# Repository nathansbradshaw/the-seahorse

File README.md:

# The Seahorse v2 

34 key keyboard with TP

Link to ZMK code https://github.com/nathansbradshaw/zmk-the-seahorse

# BOM
These are links to what I bought, not necessary to get exactly the same

## items
- 4x (12 socket) [2.54mm Sockets (Cheap) - Recommended](https://www.amazon.com/gp/product/B0778TFL39/ref=ppx_yo_dt_b_search_asin_image?ie=UTF8&psc=1) or  [2.54mm Sockets (Quality)](https://www.mouser.com/ProductDetail/Mill-Max/315-43-112-41-003000?qs=s8Nb1z4Wn%2FRfWrVqQ0TOuQ%3D%3D)

- 48x [Mill Max Pins - Recommend (Digikey)](https://www.digikey.com/en/products/detail/3320-0-00-15-00-00-03-0/4147392)

- 34x [Choc Hot Swap Sockets](https://www.boardsource.xyz/products/Choc_Hot_Swap_Sockets)

- 34x Choc Switches

- 34x Choc Key caps

- 2x Nice!Nano or equivalent

- 34x [1N4148W-7-F - Diodes](https://www.digikey.com/en/products/detail/diodes-incorporated/1N4148W-7-F/814371)

- 2x [SSSS811101 - Battery Switch](https://www.digikey.com/en/products/detail/alps-alpine/SSSS811101/19529062?s=N4IgTCBcDaIMoLgDgIxoAwpAXQL5A)

- 2x [PTS636 SL43 LFS - Reset Switch](https://www.digikey.com/en/products/detail/c-k/PTS636-SL43-LFS/10071714)

- 2x [Lithium Battery 110mAh](https://typeractive.xyz/products/lithium-battery-110mah)

- 2x [JST Battery Jack](https://typeractive.xyz/products/battery-jack)

- 1x [T460s - Track Point (12 pin RED version)]()

- 1x [2005280120 - 12 pin 1.0mm Pitch (Note: Link might be wrong)](https://www.digikey.com/en/products/detail/molex/2005280120/12142065?s=N4IgTCBcDa4AxwKxgBwFo4EYxwAQgF0BfIA)

- 2x 1.8m screw and nut

# Estimated Cost to build (Updated July 3, 2024)

|Amount| | Item                    | Cost        |Salvageable|
|----|---|-------------------------|-------------|-----------|
| 2  |   | Reset Switch            | $0.20 USD   | No  |
| 2  |   | Nice!Nano               | $50.00 USD  | Yes |
| 2  |   | Lithium Battery 110mAh  | $6.00 USD   | Yes |
| 2  |   | JST Battery Jack        | $2.00 USD   | No  |
| 2  |   | Battery Switch          | $2.50       | No  |
| 34 |   | Choc Switches           | $27.00 USD  | Yes |
| 34 |   | Hot Swap Choc Sockets   | $5.10 USD   | No  |
| 34 |   | Choc Key cap            | $11.90 USD  | Yes |
| 34 |   | Diodes                  | $5.44 USD   | No  |
| 48 |   | Mill Max Pins           | $4.76 USD   | yes-ish|
| 4  |   | 2.54mm Sockets          | $1.60 USD   | No  |
| 1  |   | PCB                     | $10.00 USD  | No  |
| 1  |   | Track Point             | $10.00 USD  | Yes |
| 1  |   | FPC Cable               | Free w/ TP  | Yes |
| 1  |   | FPC connector           | $2.00 USD   | Yes |
 
-----

 Total Cost Without TP: **$121.74 USD**

 Total Cost With TP: **$133.77 USD**

---------

 Total Cost to upgrade: **$22.10 USD**

 Total Cost to upgrade with TP: **$24.10 USD**

# Loce Alda

## BOM
- 4x [Keystone 82 battery clip](https://www.digikey.com/en/products/detail/keystone-electronics/82/227467)
- 2x [XIAO nRF52840](https://www.seeedstudio.com/Seeed-XIAO-BLE-nRF52840-p-5201.html)
- 2x [74HC595 shift register](https://www.digikey.com/en/products/detail/texas-instruments/SN74HC595N/277246)?
- 34x Choc Switches
- 34x Choc Key caps
- 34x [1N4148W-7-F - Diodes](https://www.digikey.com/en/products/detail/diodes-incorporated/1N4148W-7-F/814371)
- 2x [SSSS811101 - Battery Switch](https://www.digikey.com/en/products/detail/alps-alpine/SSSS811101/19529062?s=N4IgTCBcDaIMoLgDgIxoAwpAXQL5A)
- 2x [PTS636 SL43 LFS - Reset Switch](https://www.digikey.com/en/products/detail/c-k/PTS636-SL43-LFS/10071714)
- 1x [T460s - Track Point (12 pin RED version)]()
- 1x [2005280120 - 12 pin 1.0mm Pitch (Note: Link might be wrong)](https://www.digikey.com/en/products/detail/molex/2005280120/12142065?s=N4IgTCBcDa4AxwKxgBwFo4EYxwAQgF0BfIA)
- 2x 1.8m screw and nut

|Amount| | Item                    | Cost        |Salvageable|
|----|---|-------------------------|-------------|-----------|
| 2  |   | Reset Switch            | $0.20 USD   | No  |
| 2  |   | XIAO nRF5284            | $20.00 USD  | NO  |
| 2  |   | Battery Switch          | $2.50       | No  |
| 34 |   | Choc 
| 34 |   | Hot Swap Choc Sockets   | $5.10 USD   | No  |
| 34 |   | Choc Key cap            | $11.90 USD  | Yes |
| 34 |   | Diodes                  | $5.44 USD   | No  |
| 1  |   | PCB                     | $10.00 USD  | No  |
| 1  |   | Track Point             | $10.00 USD  | Yes |
| 1  |   | FPC Cable               | Free w/ TP  | Yes |
| 1  |   | FPC connector           | $2.00 USD   | Yes |
| 2  |   | 74HC595 Shift Register  | $3.00 USD   | No  |
| 4  |   | Keystone 82 battery clip| $1.50 USD   | NO  |
| 2  |   | 10440 Lithium battery   | $5          | Yes |

-----

 Total Cost Without TP: **$64.91 USD**

 Total Cost With TP: **$76.91 USD**

---------

 Total Cost to upgrade: **$45.24 USD**

 Total Cost to upgrade with TP: **$47.24 USD**

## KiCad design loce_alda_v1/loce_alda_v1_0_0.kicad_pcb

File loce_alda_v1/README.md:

# The Seahorse v2 

34 key keyboard with TP

Link to ZMK code https://github.com/nathansbradshaw/zmk-the-seahorse

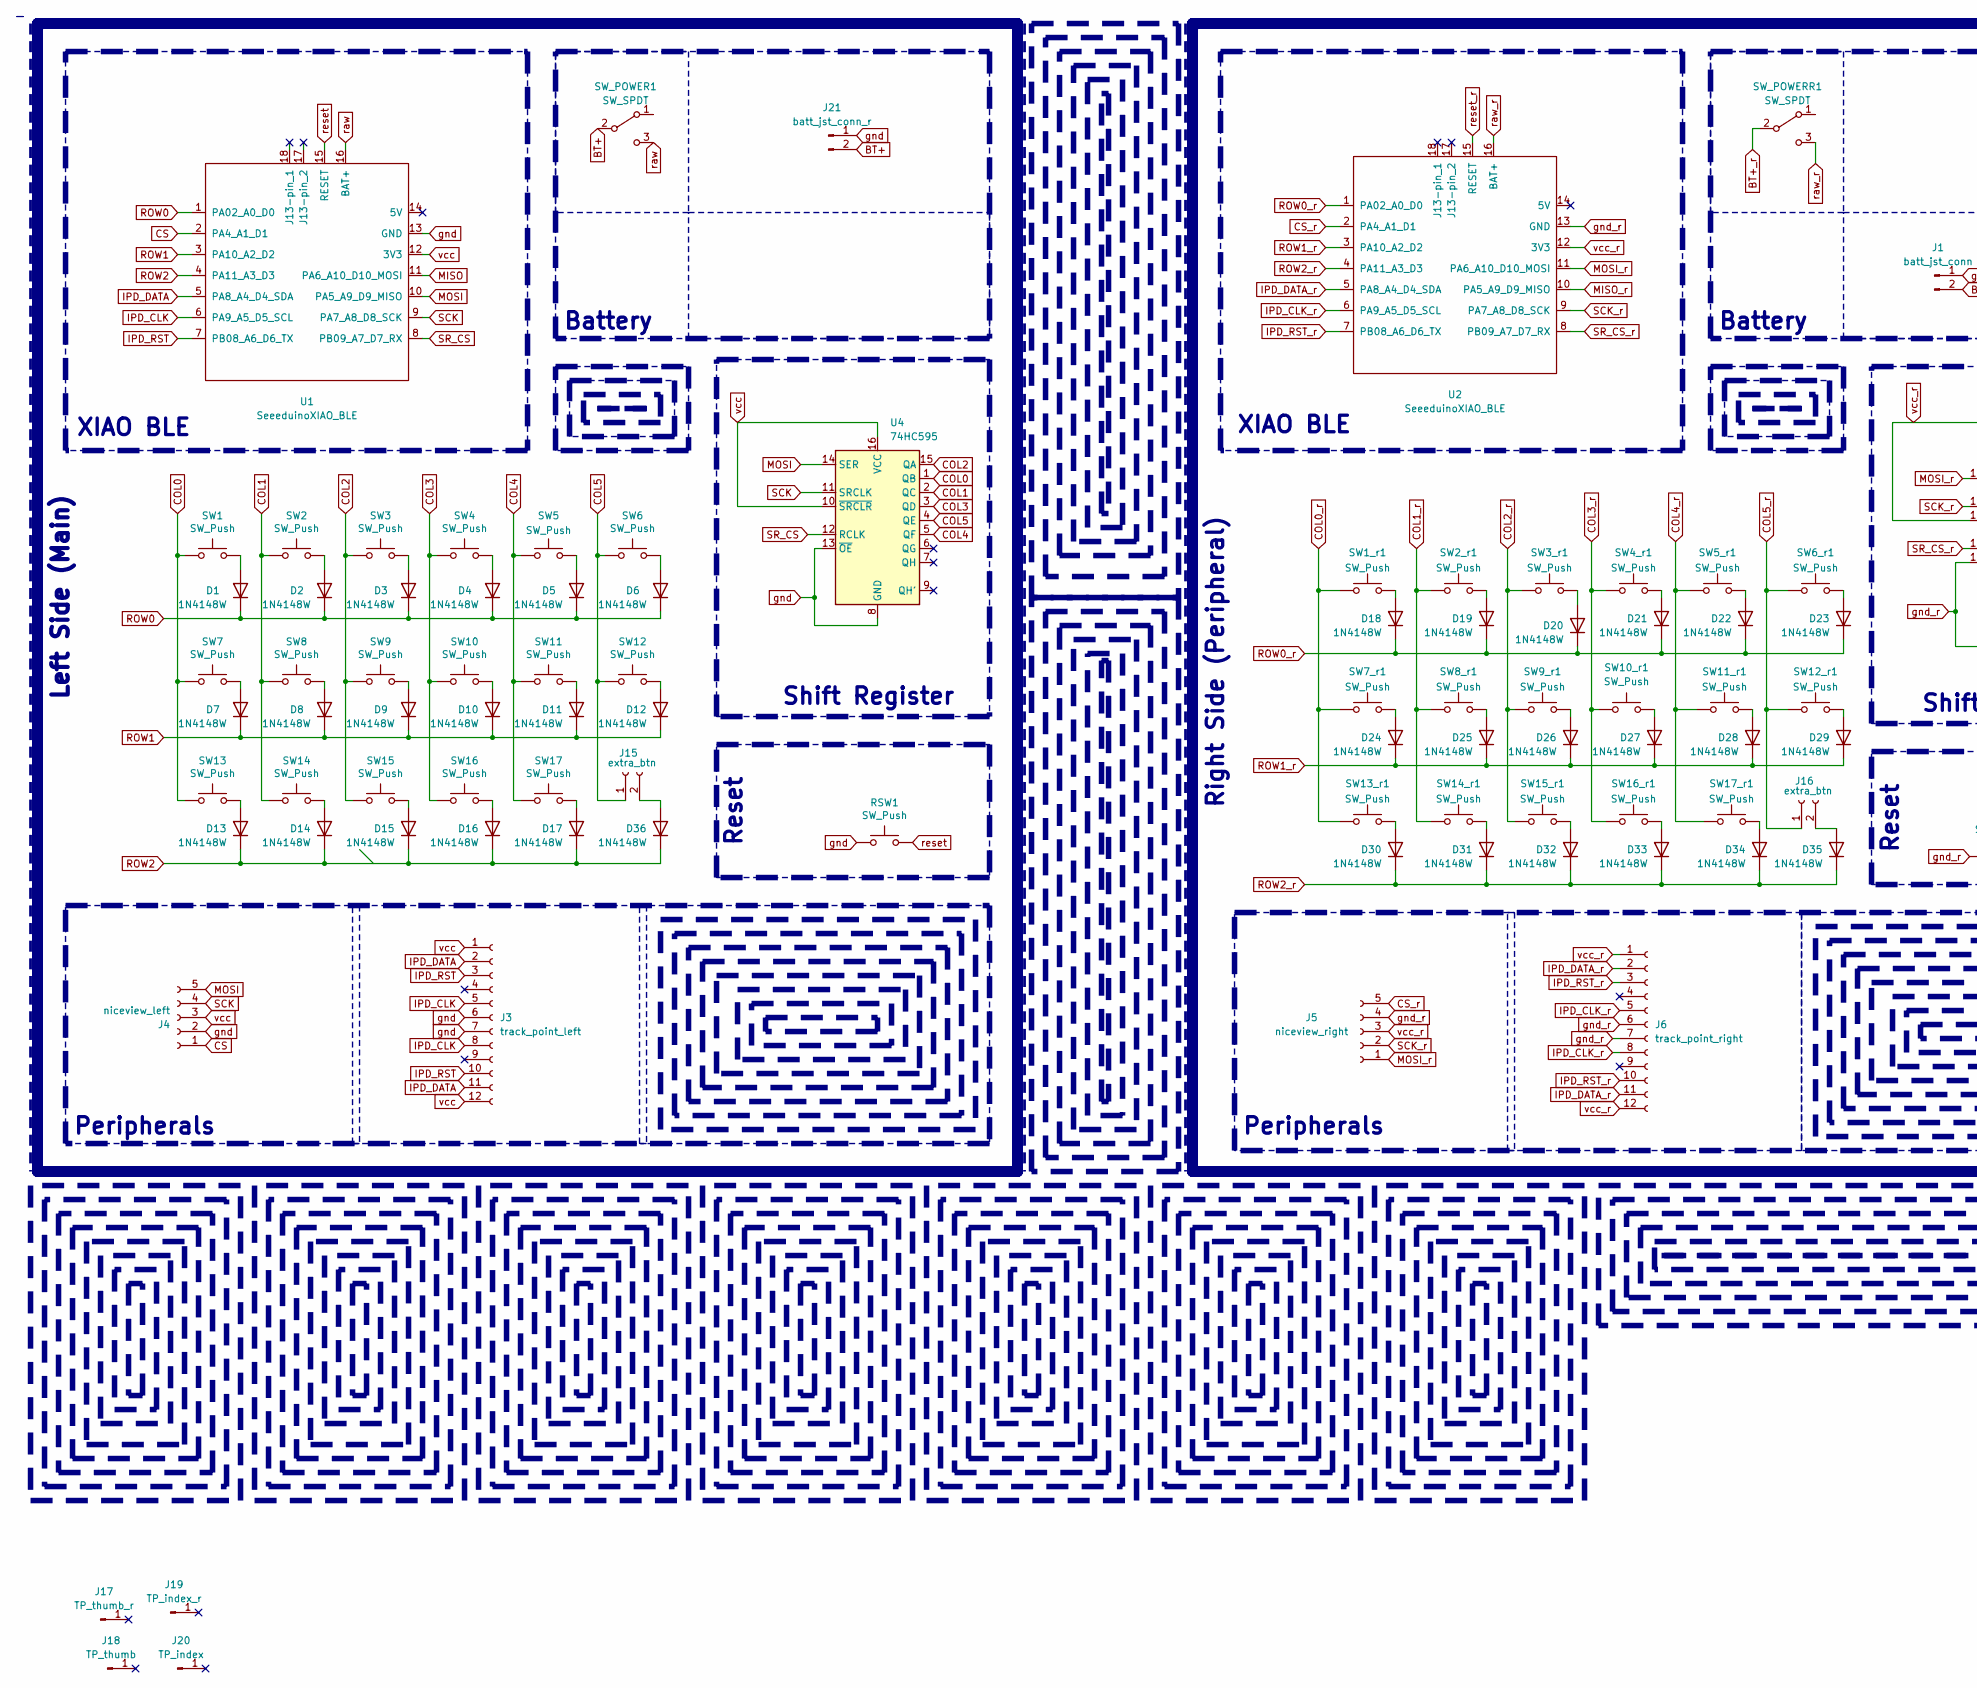
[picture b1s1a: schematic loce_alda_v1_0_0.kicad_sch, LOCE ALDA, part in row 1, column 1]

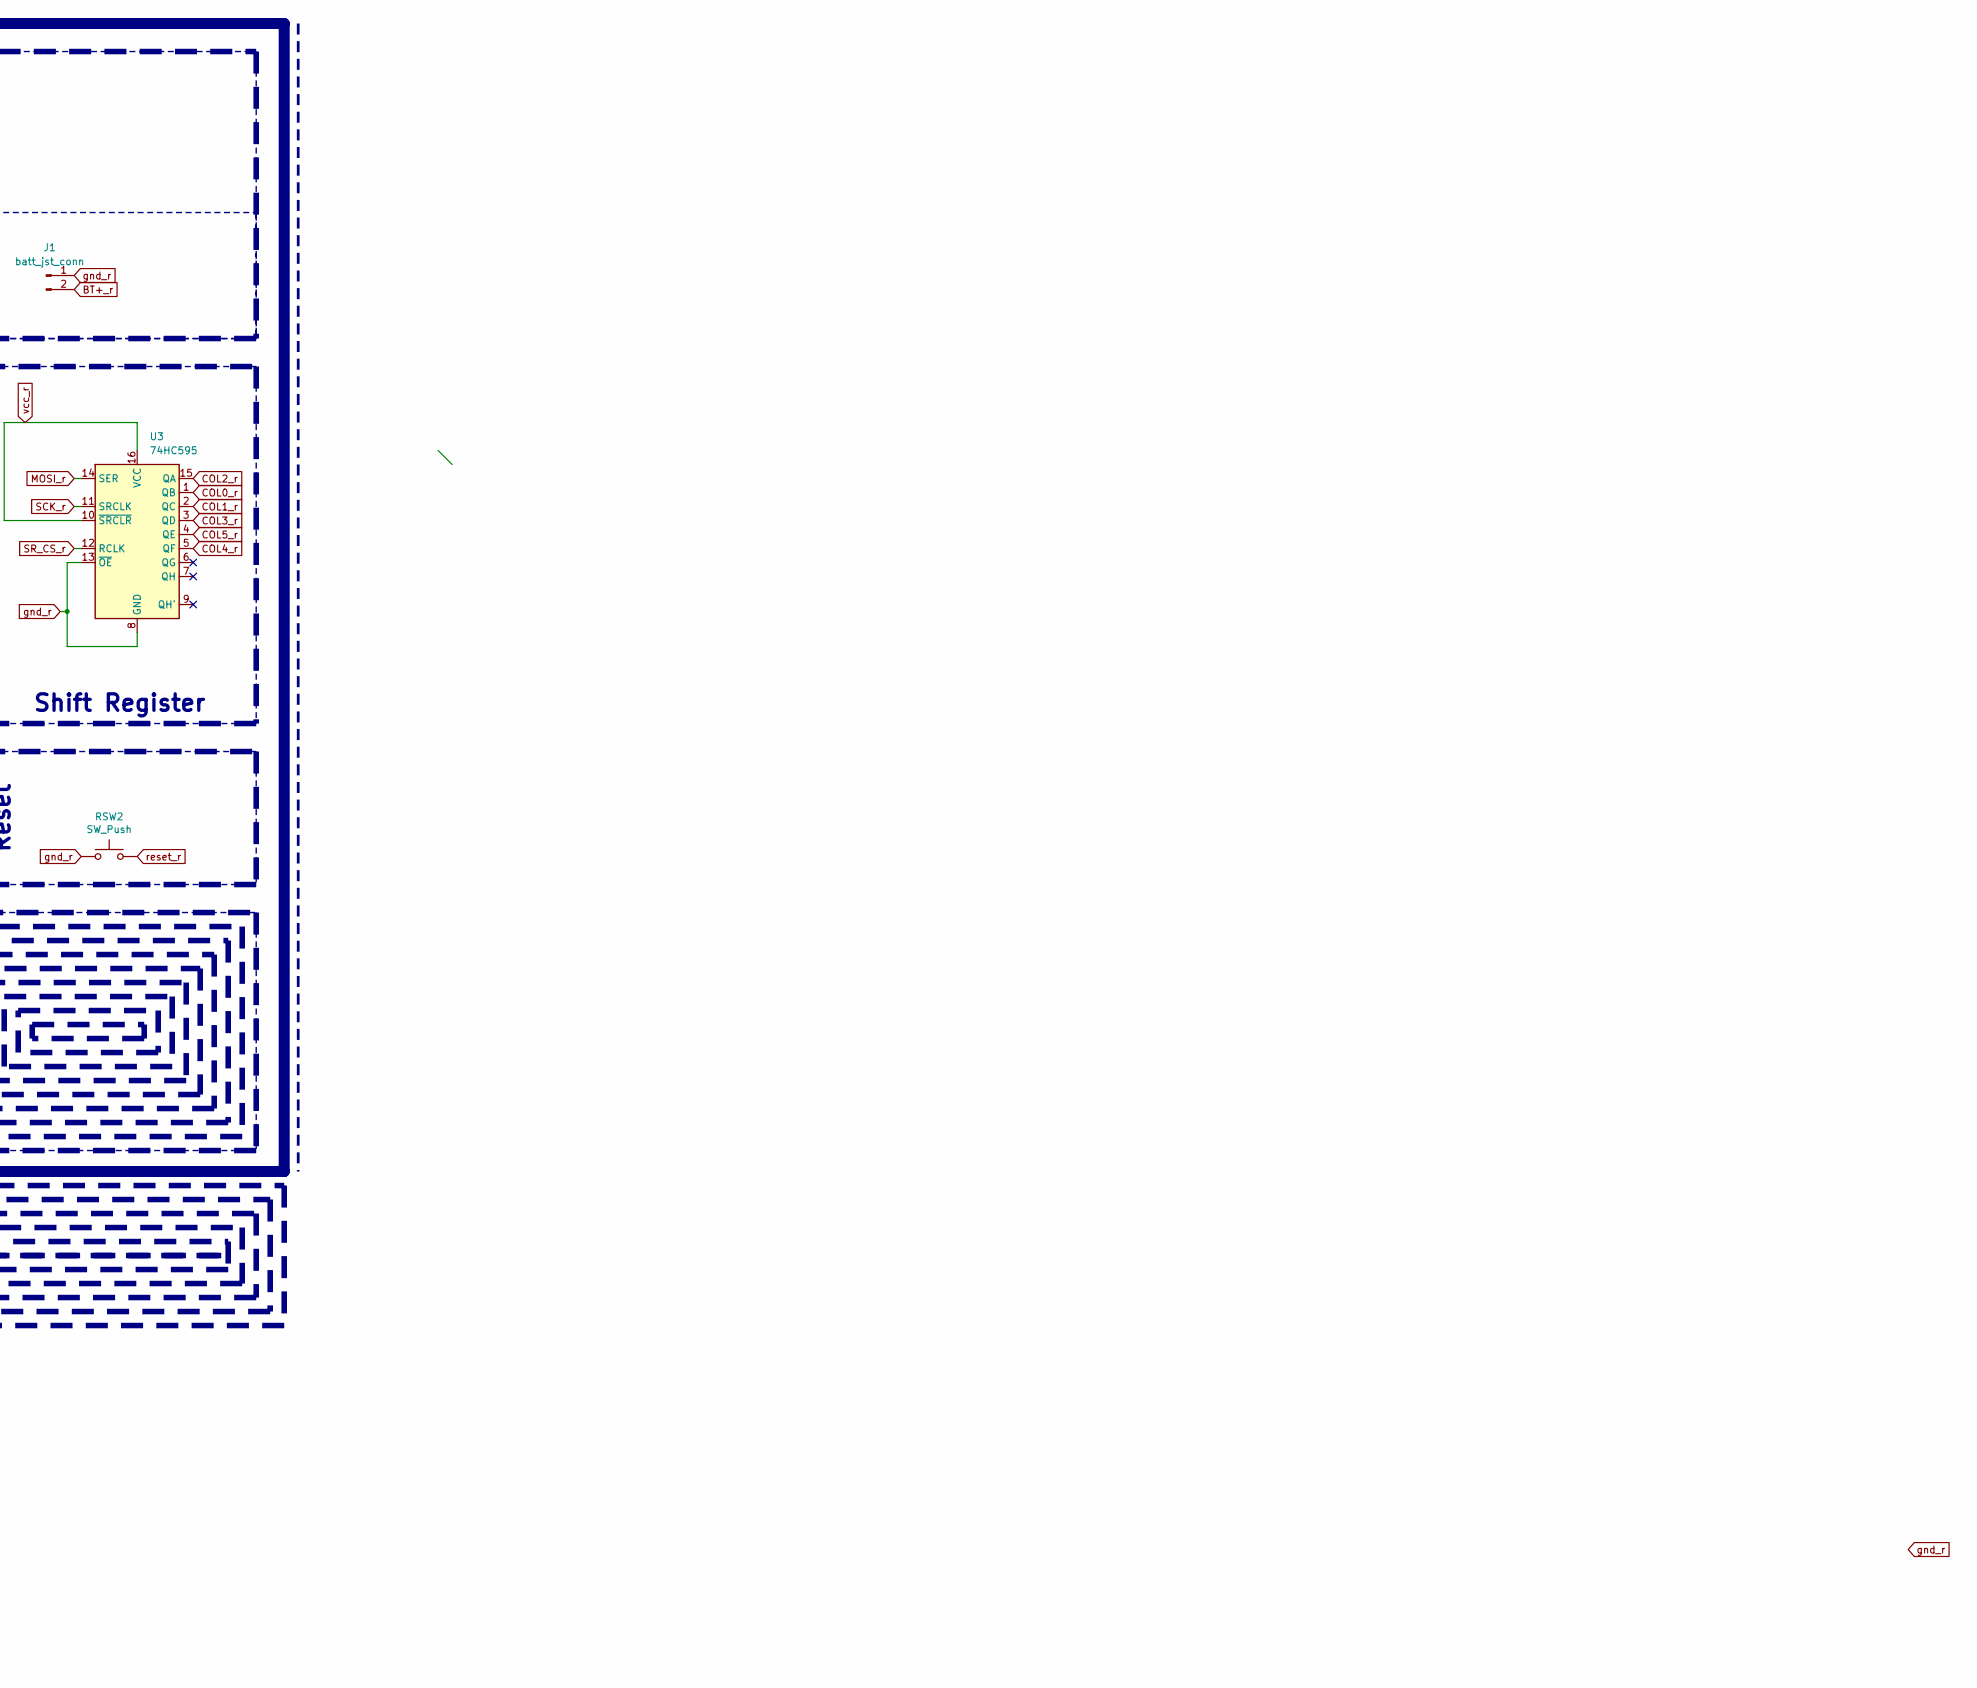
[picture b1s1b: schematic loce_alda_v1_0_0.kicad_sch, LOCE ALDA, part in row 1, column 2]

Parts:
D1, D2, D3, D4, D5, D6, D7, D8, D9, D10, D11, D12, D13, D14, D15, D16, D17, D18, D19, D20, D21, D22, D23, D24, D25, D26, D27, D28, D29, D30, D31, D32, D33, D34, D35, D36: 1N4148W; D_SOD-123
J1: batt_jst_conn; JST_PH_S2B-PH-K_1x02_P2.00mm_Horizontal
J3: track_point_left; TE_1-84953-2_1x12-1MP_P1.0mm_Horizontal
J4: niceview_left; PinHeader_1x05_P2.54mm_Vertical
J5: niceview_right; PinHeader_1x05_P2.54mm_Vertical
J6: track_point_right; TE_1-84953-2_1x12-1MP_P1.0mm_Horizontal
J15, J16: extra_btn; PinSocket_1x02_P2.54mm_Vertical
J17: TP_thumb_r; trackpoint_mount_t460s_offset
J18: TP_thumb; trackpoint_mount_t460s_offset
J19: TP_index_r; trackpoint_mount_t460s_offset
J20: TP_index; trackpoint_mount_t460s_offset
J21: batt_jst_conn_r; JST_PH_S2B-PH-K_1x02_P2.00mm_Horizontal
RSW1, RSW2: SW_Push; Panasonic_EVQPUL_EVQPUC
SW1, SW1_r1, SW2, SW2_r1, SW3, SW3_r1, SW4, SW4_r1, SW5, SW5_r1, SW7, SW7_r1, SW8, SW8_r1, SW9, SW9_r1, SW10, SW10_r1, SW11, SW11_r1, SW12, SW12_r1, SW13, SW13_r1, SW14, SW14_r1, SW15, SW15_r1, SW16, SW16_r1, SW17, SW17_r1: SW_Push; SW_Hotswap_Kailh_Choc_V1_tweaked_no_clickbar
SW6, SW6_r1: SW_Push; SW_Hotswap_Kailh_Choc_V1_tweaked_23du
SW_POWER1: SW_SPDT; SPDT_C128955
SW_POWERR1: SW_SPDT; SPDT_C128955
U1, U2: SeeeduinoXIAO_BLE; XIAO-nRF52840-SMD
U3, U4: 74HC595; D0016A_N

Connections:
BT+: J21.2, SW_POWER1.2 (B)
BT+_r: J1.2, SW_POWERR1.2 (B)
COL0: SW1.1, SW7.1, SW13.1, U4.1 (QB)
COL0_r: SW1_r1.1, SW7_r1.1, SW13_r1.1, U3.1 (QB)
COL1: SW2.1, SW8.1, SW14.1, U4.2 (QC)
COL1_r: SW2_r1.1, SW8_r1.1, SW14_r1.1, U3.2 (QC)
COL2: SW3.1, SW9.1, SW15.1, U4.15 (QA)
COL2_r: SW3_r1.1, SW9_r1.1, SW15_r1.1, U3.15 (QA)
COL3: SW4.1, SW10.1, SW16.1, U4.3 (QD)
COL3_r: SW4_r1.1, SW10_r1.1, SW16_r1.1, U3.3 (QD)
COL4: SW5.1, SW11.1, SW17.1, U4.5 (QF); also elsewhere on the board
COL4_r: SW5_r1.1, SW11_r1.1, SW17_r1.1, U3.5 (QF); also elsewhere on the board
COL5: J15.1, SW6.1, SW12.1, U4.4 (QE)
COL5_r: J16.1, SW6_r1.1, SW12_r1.1, U3.4 (QE)
CS: J4.1, U1.2 (PA4_A1_D1)
CS_r: J5.5, U2.2 (PA4_A1_D1)
IPD_CLK: J3.5, J3.8, U1.6 (PA9_A5_D5_SCL)
IPD_CLK_r: J6.5, J6.8, U2.6 (PA9_A5_D5_SCL)
IPD_DATA: J3.2, J3.11, U1.5 (PA8_A4_D4_SDA)
IPD_DATA_r: J6.2, J6.11, U2.5 (PA8_A4_D4_SDA)
IPD_RST: J3.3, J3.10, U1.7 (PB08_A6_D6_TX)
IPD_RST_r: J6.3, J6.10, U2.7 (PB08_A6_D6_TX)
MISO: U1.11 (PA6_A10_D10_MOSI)
MISO_r: U2.10 (PA5_A9_D9_MISO)
MOSI: J4.5, U1.10 (PA5_A9_D9_MISO), U4.14 (SER)
MOSI_r: J5.1, U2.11 (PA6_A10_D10_MOSI), U3.14 (SER)
unnamed: D1.2 (A), SW1.2
unnamed: D2.2 (A), SW2.2
unnamed: D3.2 (A), SW3.2
unnamed: D4.2 (A), SW4.2
unnamed: D5.2 (A), SW5.2
unnamed: D6.2 (A), SW6.2
unnamed: D7.2 (A), SW7.2
unnamed: D8.2 (A), SW8.2
unnamed: D9.2 (A), SW9.2
unnamed: D10.2 (A), SW10.2
unnamed 36: D11.2 (A), SW11.2; also elsewhere on the board
unnamed: D12.2 (A), SW12.2
unnamed: D13.2 (A), SW13.2
unnamed: D14.2 (A), SW14.2
unnamed: D15.2 (A), SW15.2
unnamed: D16.2 (A), SW16.2
unnamed: D17.2 (A), SW17.2
unnamed: D18.2 (A), SW1_r1.2
unnamed: D19.2 (A), SW2_r1.2
unnamed: D20.2 (A), SW3_r1.2
unnamed: D21.2 (A), SW4_r1.2
unnamed: D22.2 (A), SW5_r1.2
unnamed: D23.2 (A), SW6_r1.2
unnamed: D24.2 (A), SW7_r1.2
unnamed: D25.2 (A), SW8_r1.2
unnamed: D26.2 (A), SW9_r1.2
unnamed: D27.2 (A), SW10_r1.2
unnamed 53: D28.2 (A), SW11_r1.2; also elsewhere on the board
unnamed: D29.2 (A), SW12_r1.2
unnamed: D30.2 (A), SW13_r1.2
unnamed: D31.2 (A), SW14_r1.2
unnamed: D32.2 (A), SW15_r1.2
unnamed: D33.2 (A), SW16_r1.2
unnamed: D34.2 (A), SW17_r1.2
unnamed: D35.2 (A), J16.2
unnamed: D36.2 (A), J15.2
ROW0: D1.1 (K), D2.1 (K), D3.1 (K), D4.1 (K), D5.1 (K), D6.1 (K), U1.1 (PA02_A0_D0)
ROW0_r: D18.1 (K), D19.1 (K), D20.1 (K), D21.1 (K), D22.1 (K), D23.1 (K), U2.1 (PA02_A0_D0)
ROW1: D7.1 (K), D8.1 (K), D9.1 (K), D10.1 (K), D11.1 (K), D12.1 (K), U1.3 (PA10_A2_D2)
ROW1_r: D24.1 (K), D25.1 (K), D26.1 (K), D27.1 (K), D28.1 (K), D29.1 (K), U2.3 (PA10_A2_D2)
ROW2: D13.1 (K), D14.1 (K), D15.1 (K), D16.1 (K), D17.1 (K), D36.1 (K), U1.4 (PA11_A3_D3)
ROW2_r: D30.1 (K), D31.1 (K), D32.1 (K), D33.1 (K), D34.1 (K), D35.1 (K), U2.4 (PA11_A3_D3)
SCK: J4.4, U1.9 (PA7_A8_D8_SCK), U4.11 (SRCLK)
SCK_r: J5.2, U2.9 (PA7_A8_D8_SCK), U3.11 (SRCLK)
SR_CS: U1.8 (PB09_A7_D7_RX), U4.12 (RCLK)
SR_CS_r: U2.8 (PB09_A7_D7_RX), U3.12 (RCLK)
gnd: J3.6, J3.7, J4.2, J21.1, RSW1.1, U1.13 (GND), U4.8 (GND), U4.13 (~OE)
gnd_r: J1.1, J5.4, J6.6, J6.7, RSW2.1, U2.13 (GND), U3.8 (GND), U3.13 (~OE)
raw: SW_POWER1.3 (C), U1.16 (BAT+)
raw_r: SW_POWERR1.3 (C), U2.16 (BAT+)
reset: RSW1.2, U1.15 (RESET)
reset_r: RSW2.2, U2.15 (RESET)
vcc: J3.1, J3.12, J4.3, U1.12 (3V3), U4.10 (~SRCLR), U4.16 (VCC)
vcc_r: J5.3, J6.1, J6.12, U2.12 (3V3), U3.10 (~SRCLR), U3.16 (VCC)

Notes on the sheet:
Peripherals
Right Side (Peripheral)
XIAO BLE
Battery
Left Side (Main)
Shift Register
Reset

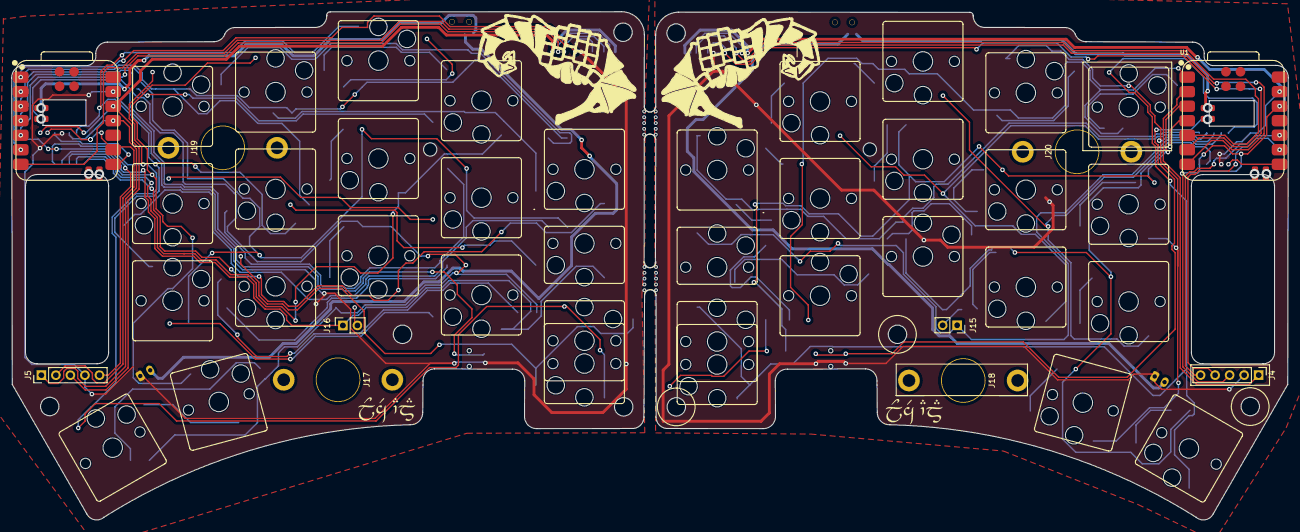
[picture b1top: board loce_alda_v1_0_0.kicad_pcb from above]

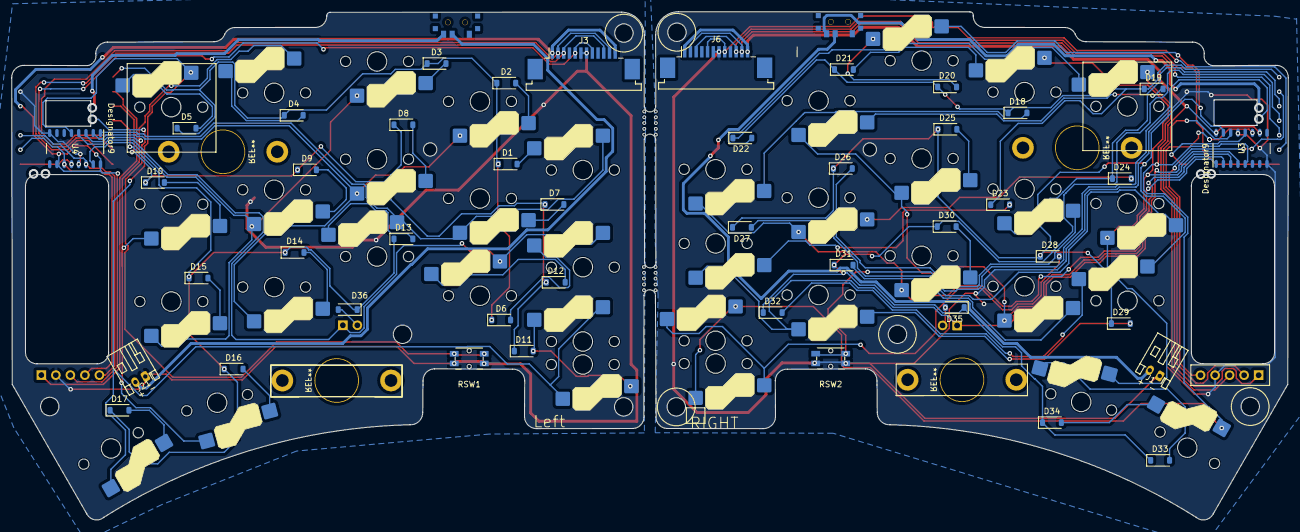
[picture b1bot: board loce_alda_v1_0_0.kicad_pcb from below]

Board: 2 copper layers, 223.3 x 88.9 mm, 94 parts (46 on the bottom side), 78 nets.

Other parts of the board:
SW11#2, SW11_r1#2: SW_Push; SW_Hotswap_Kailh_Choc_V1_tweaked_no_clickbar
mouse-bite-2mm-slot1, mouse-bite-2mm-slot1#2: VAL**; mouse-bite-5mm-slot-with-space-for-track

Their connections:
COL4: SW11#2.1; also elsewhere on the board
COL4_r: SW11_r1#2.1; also elsewhere on the board
unnamed 36: SW11#2.2; also elsewhere on the board
unnamed 53: SW11_r1#2.2; also elsewhere on the board

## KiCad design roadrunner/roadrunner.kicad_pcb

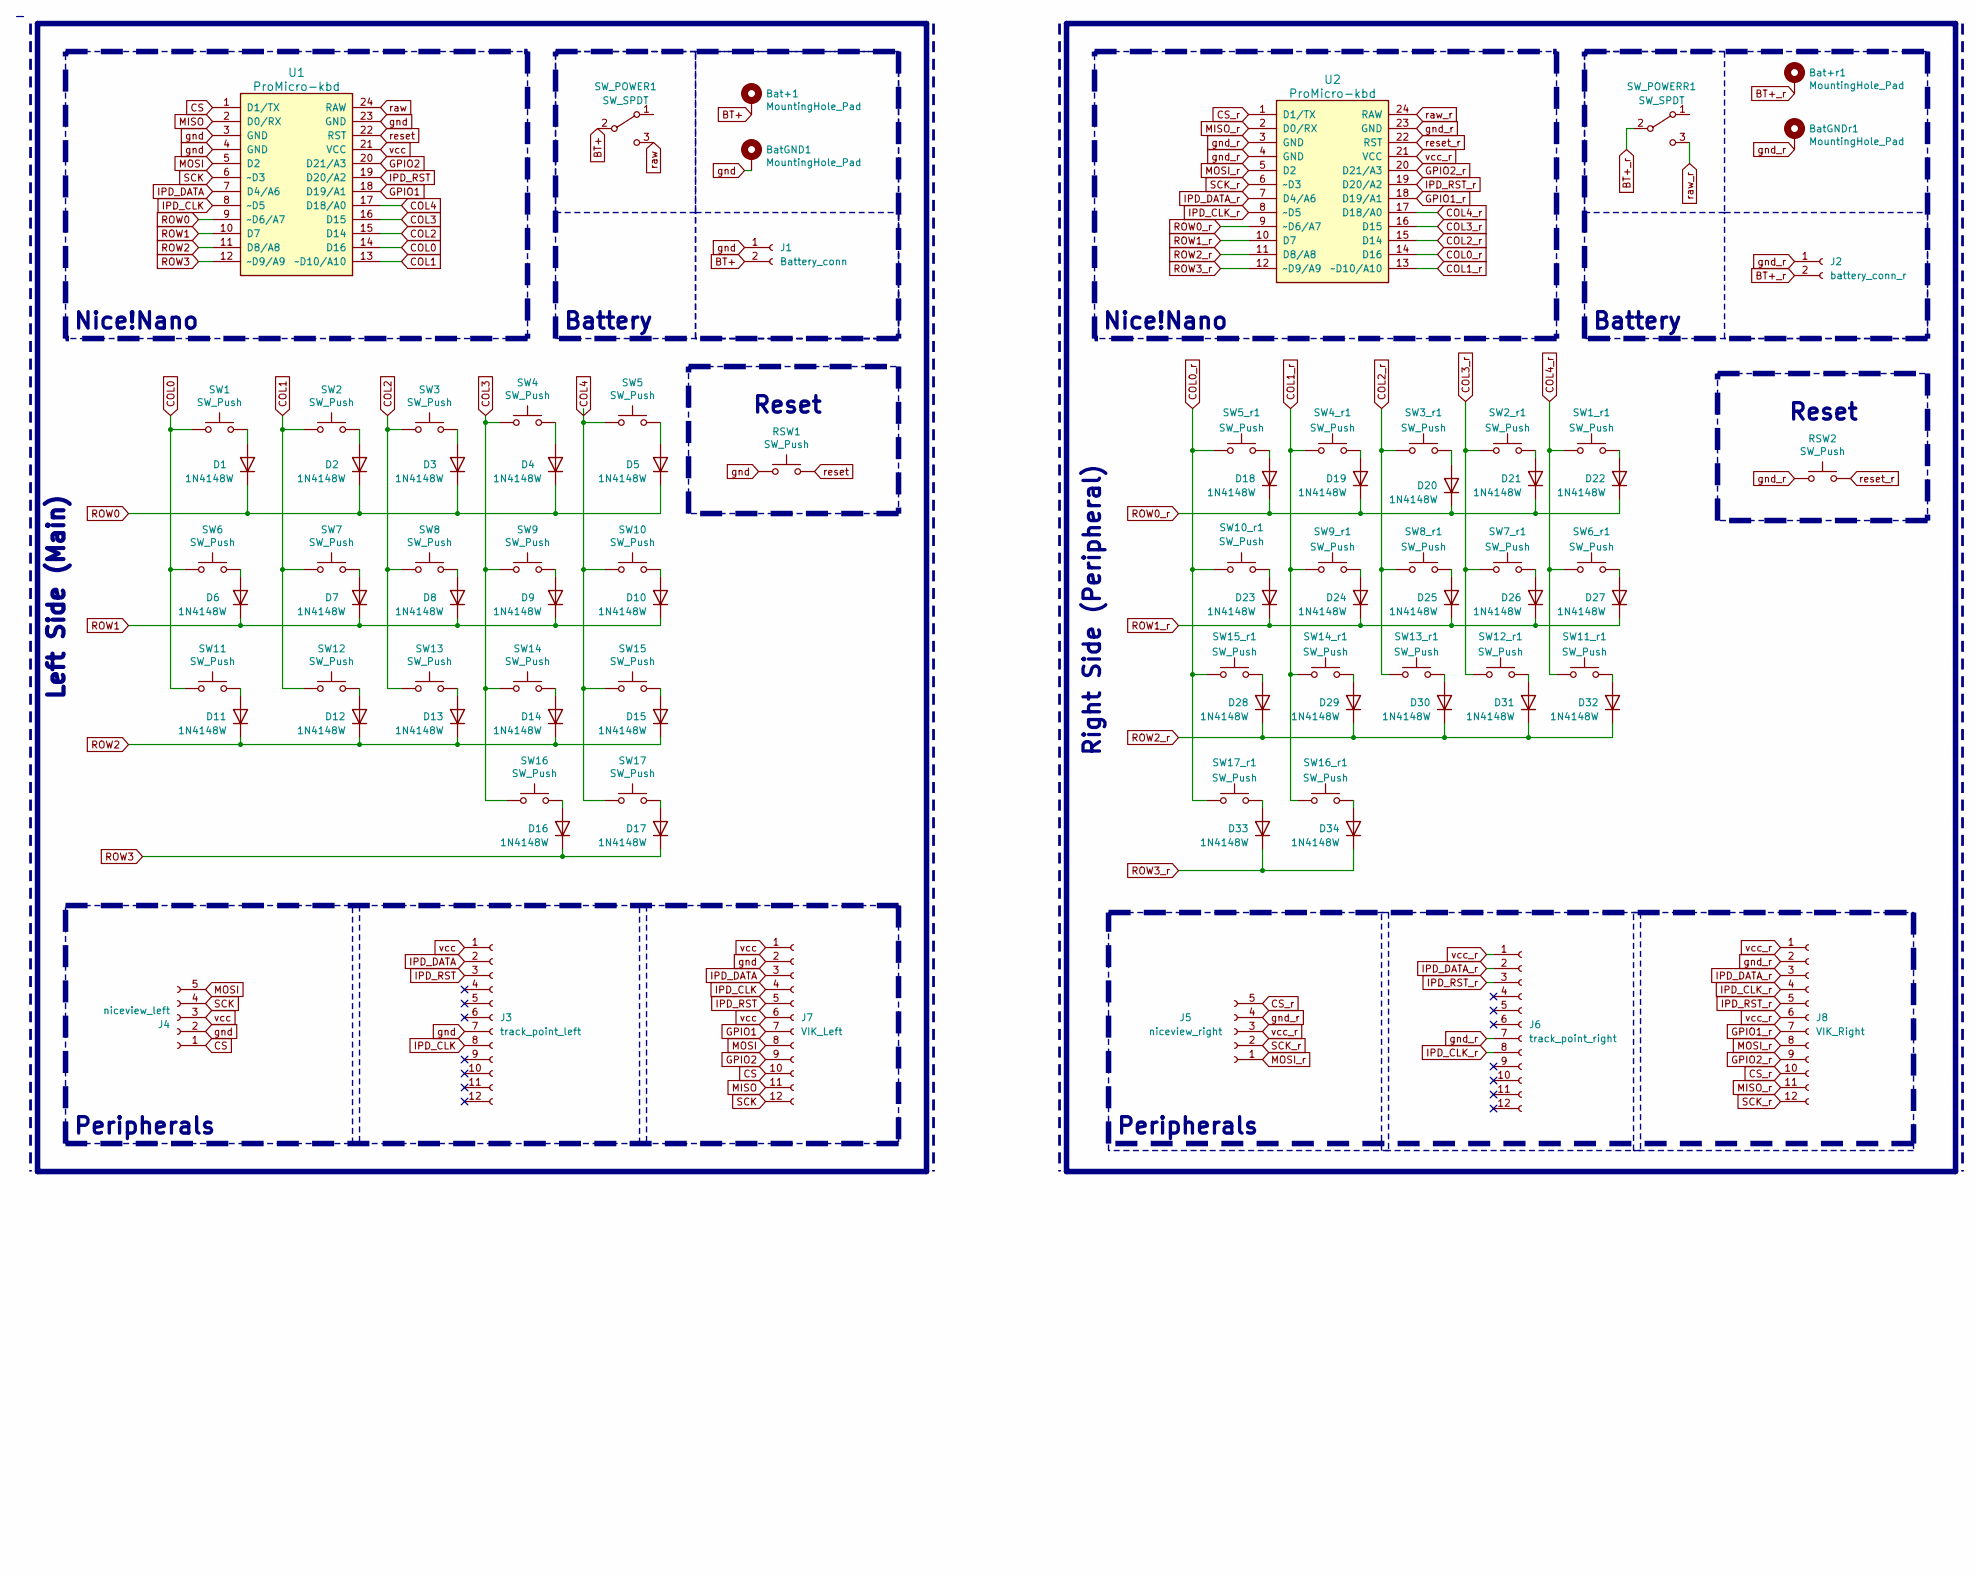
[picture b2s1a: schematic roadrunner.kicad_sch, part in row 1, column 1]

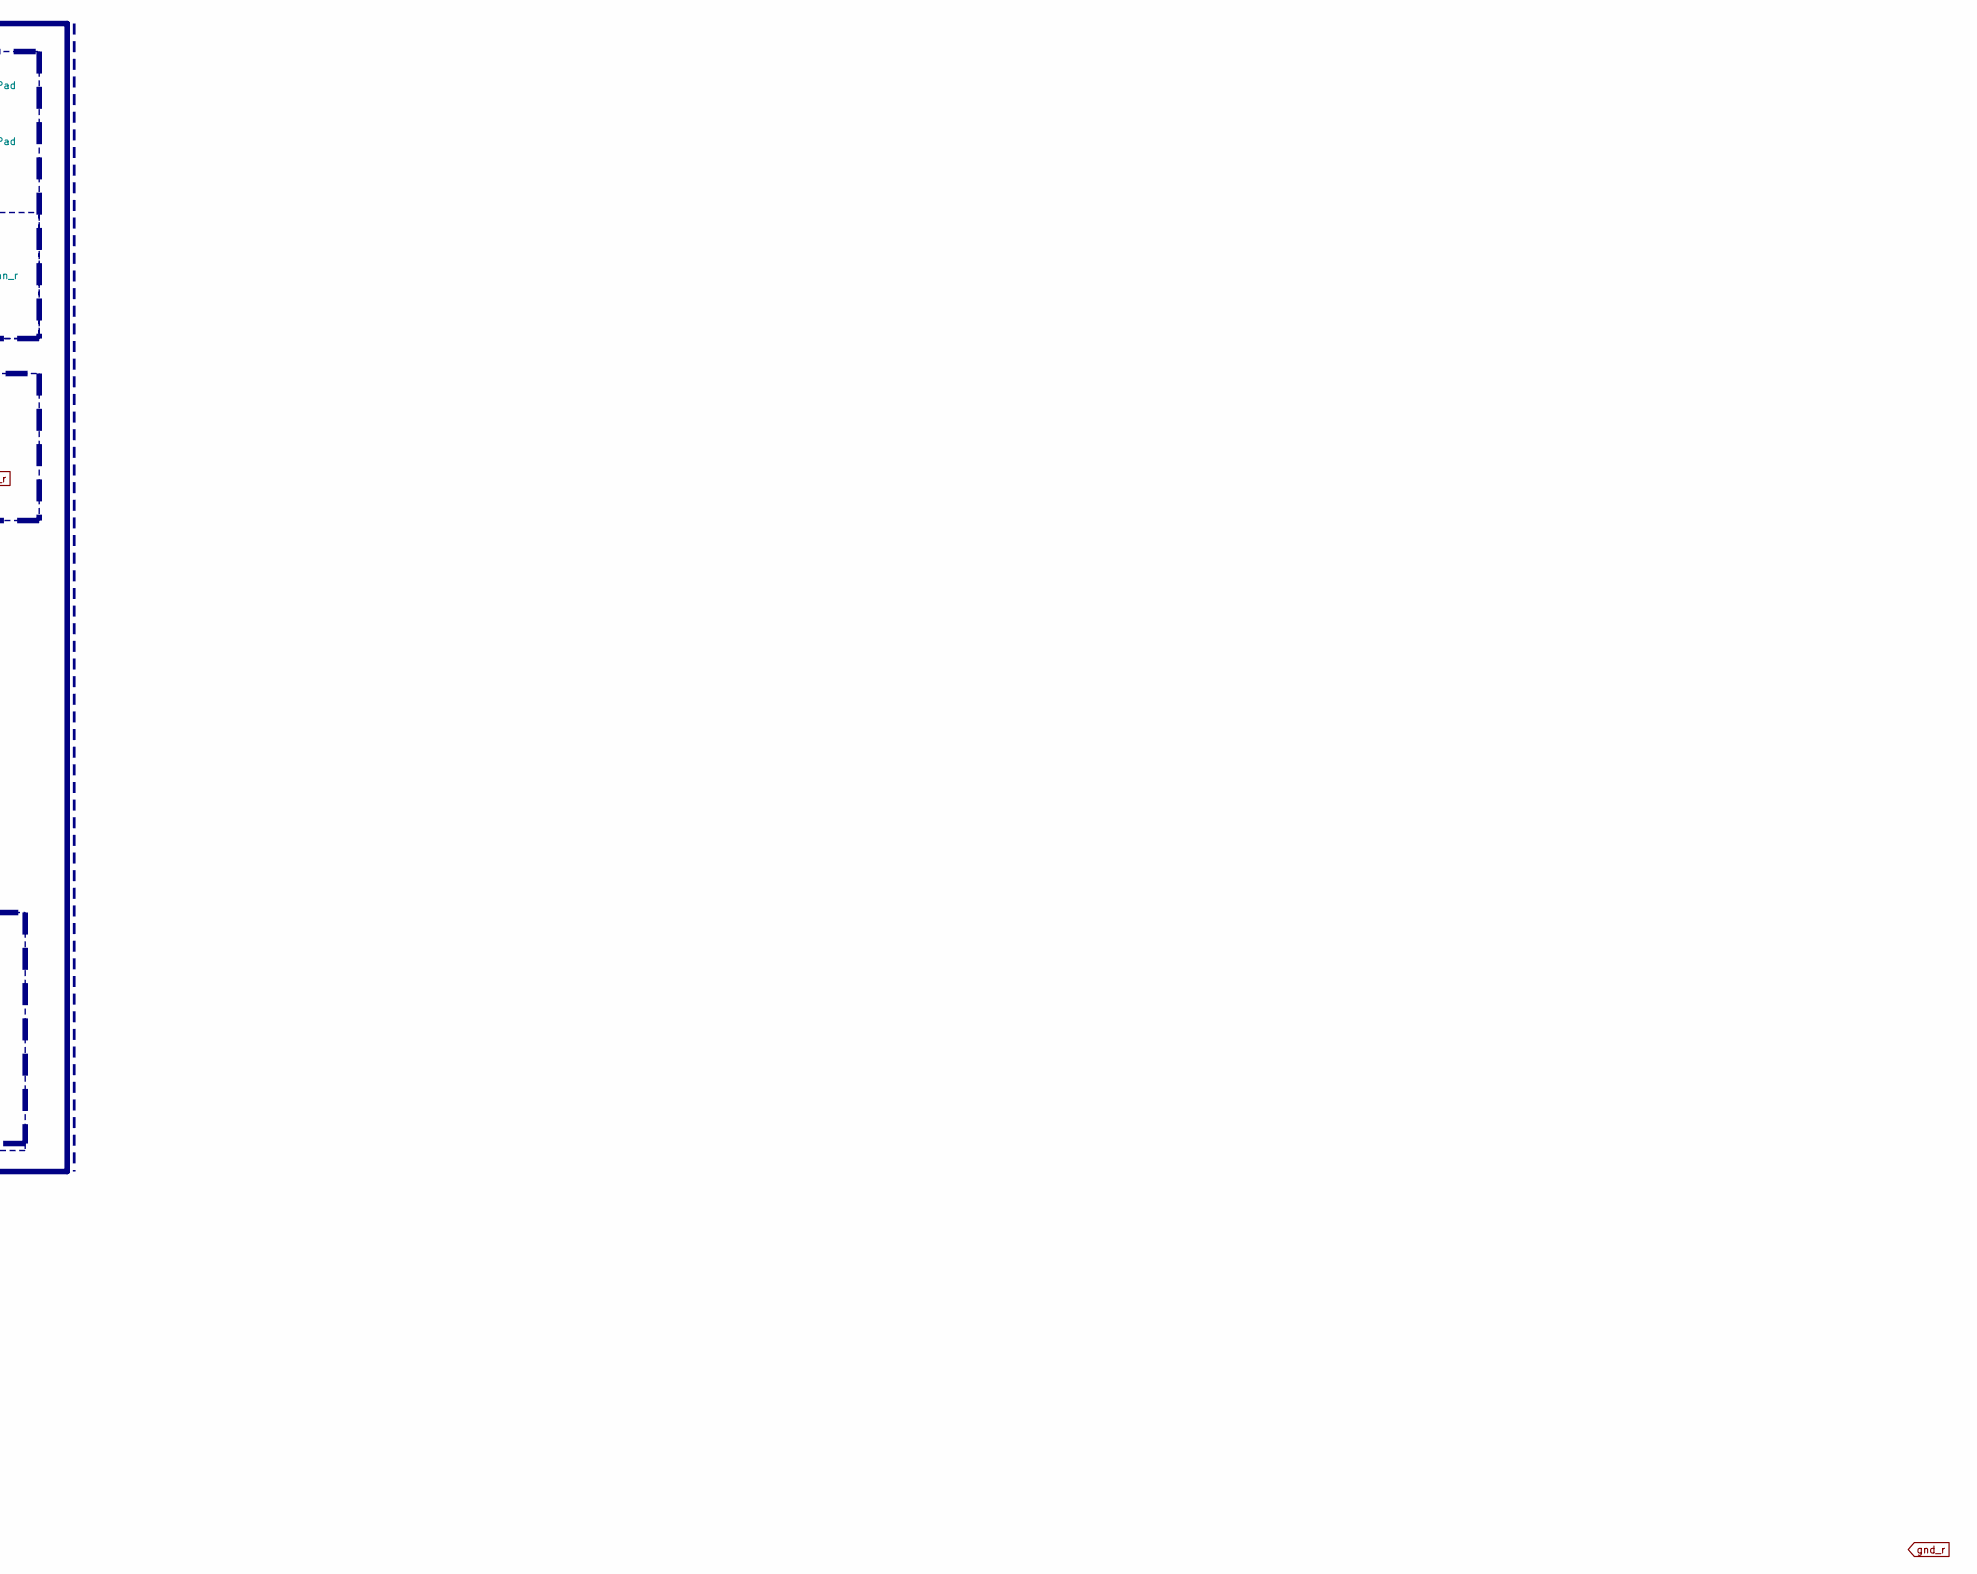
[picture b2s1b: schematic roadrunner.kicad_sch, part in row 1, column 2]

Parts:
Bat+1: MountingHole_Pad; 1pin_conn
Bat+r1: MountingHole_Pad; 1pin_conn
BatGND1: MountingHole_Pad; 1pin_conn
BatGNDr1: MountingHole_Pad; 1pin_conn
D1, D2, D3, D4, D5, D6, D7, D8, D9, D10, D11, D12, D13, D14, D15, D16, D17, D18, D19, D20, D21, D22, D23, D24, D25, D26, D27, D28, D29, D30, D31, D32, D33, D34: 1N4148W; D_SOD-123
J1: Battery_conn; JST_PH_S2B-PH-K_1x02_P2.00mm_Horizontal
J2: battery_conn_r; JST_PH_S2B-PH-K_1x02_P2.00mm_Horizontal
J3: track_point_left; TE_1-84953-2_1x12-1MP_P1.0mm_Horizontal
J4: niceview_left; PinHeader_1x05_P2.54mm_Vertical
J5: niceview_right; PinHeader_1x05_P2.54mm_Vertical
J6: track_point_right; TE_1-84953-2_1x12-1MP_P1.0mm_Horizontal
J7: VIK_Left; Hirose_FH12-12S-0.5SH_1x12-1MP_P0.50mm_Horizontal
J8: VIK_Right; Hirose_FH12-12S-0.5SH_1x12-1MP_P0.50mm_Horizontal
RSW1, RSW2: SW_Push; PTS636SP43LFS
SW1, SW1_r1, SW2, SW2_r1, SW3, SW3_r1, SW4, SW4_r1, SW5, SW5_r1, SW6, SW6_r1, SW7, SW7_r1, SW8, SW8_r1, SW9, SW9_r1, SW10, SW10_r1, SW11, SW11_r1, SW12, SW12_r1, SW13, SW13_r1, SW14, SW14_r1, SW15, SW15_r1, SW16, SW16_r1, SW17, SW17_r1: SW_Push; SW_Hotswap_Kailh_Choc_V1_tweaked
SW_POWER1: SW_SPDT; SPDT_C128955
SW_POWERR1: SW_SPDT; SPDT_C128955
U1, U2: ProMicro-kbd; Sparkfun_Pro_Micro

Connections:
BT+: Bat+1.1, J1.2, SW_POWER1.2 (B)
BT+_r: Bat+r1.1, J2.2, SW_POWERR1.2 (B)
COL0: SW1.1, SW6.1, SW11.1, U1.14 (D16)
COL0_r: SW5_r1.1, SW10_r1.1, SW15_r1.1, SW17_r1.1, U2.14 (D16)
COL1: SW2.1, SW7.1, SW12.1, U1.13 (~D10/A10)
COL1_r: SW4_r1.1, SW9_r1.1, SW14_r1.1, SW16_r1.1, U2.13 (~D10/A10)
COL2: SW3.1, SW8.1, SW13.1, U1.15 (D14)
COL2_r: SW3_r1.1, SW8_r1.1, SW13_r1.1, U2.15 (D14)
COL3: SW4.1, SW9.1, SW14.1, SW16.1, U1.16 (D15)
COL3_r: SW2_r1.1, SW7_r1.1, SW12_r1.1, U2.16 (D15)
COL4: SW5.1, SW10.1, SW15.1, SW17.1, U1.17 (D18/A0)
COL4_r: SW1_r1.1, SW6_r1.1, SW11_r1.1, U2.17 (D18/A0)
CS: J4.1, J7.10, U1.1 (D1/TX)
CS_r: J5.5, J8.10, U2.1 (D1/TX)
GPIO1: J7.7, U1.18 (D19/A1)
GPIO1_r: J8.7, U2.18 (D19/A1)
GPIO2: J7.9, U1.20 (D21/A3)
GPIO2_r: J8.9, U2.20 (D21/A3)
IPD_CLK: J3.8, J7.4, U1.8 (~D5)
IPD_CLK_r: J6.8, J8.4, U2.8 (~D5)
IPD_DATA: J3.2, J7.3, U1.7 (D4/A6)
IPD_DATA_r: J6.2, J8.3, U2.7 (D4/A6)
IPD_RST: J3.3, J7.5, U1.19 (D20/A2)
IPD_RST_r: J6.3, J8.5, U2.19 (D20/A2)
MISO: J7.11, U1.2 (D0/RX)
MISO_r: J8.11, U2.2 (D0/RX)
MOSI: J4.5, J7.8, U1.5 (D2)
MOSI_r: J5.1, J8.8, U2.5 (D2)
unnamed: D1.2 (A), SW1.2
unnamed: D2.2 (A), SW2.2
unnamed: D3.2 (A), SW3.2
unnamed: D4.2 (A), SW4.2
unnamed: D5.2 (A), SW5.2
unnamed: D6.2 (A), SW6.2
unnamed: D7.2 (A), SW7.2
unnamed: D8.2 (A), SW8.2
unnamed: D9.2 (A), SW9.2
unnamed: D10.2 (A), SW10.2
unnamed: D11.2 (A), SW11.2
unnamed: D12.2 (A), SW12.2
unnamed: D13.2 (A), SW13.2
unnamed: D14.2 (A), SW14.2
unnamed: D15.2 (A), SW15.2
unnamed: D16.2 (A), SW16.2
unnamed: D17.2 (A), SW17.2
unnamed: D18.2 (A), SW5_r1.2
unnamed: D19.2 (A), SW4_r1.2
unnamed: D20.2 (A), SW3_r1.2
unnamed: D21.2 (A), SW2_r1.2
unnamed: D22.2 (A), SW1_r1.2
unnamed: D23.2 (A), SW10_r1.2
unnamed: D24.2 (A), SW9_r1.2
unnamed: D25.2 (A), SW8_r1.2
unnamed: D26.2 (A), SW7_r1.2
unnamed: D27.2 (A), SW6_r1.2
unnamed: D28.2 (A), SW15_r1.2
unnamed: D29.2 (A), SW14_r1.2
unnamed: D30.2 (A), SW13_r1.2
unnamed: D31.2 (A), SW12_r1.2
unnamed: D32.2 (A), SW11_r1.2
unnamed: D33.2 (A), SW17_r1.2
unnamed: D34.2 (A), SW16_r1.2
ROW0: D1.1 (K), D2.1 (K), D3.1 (K), D4.1 (K), D5.1 (K), U1.9 (~D6/A7)
ROW0_r: D18.1 (K), D19.1 (K), D20.1 (K), D21.1 (K), D22.1 (K), U2.9 (~D6/A7)
ROW1: D6.1 (K), D7.1 (K), D8.1 (K), D9.1 (K), D10.1 (K), U1.10 (D7)
ROW1_r: D23.1 (K), D24.1 (K), D25.1 (K), D26.1 (K), D27.1 (K), U2.10 (D7)
ROW2: D11.1 (K), D12.1 (K), D13.1 (K), D14.1 (K), D15.1 (K), U1.11 (D8/A8)
ROW2_r: D28.1 (K), D29.1 (K), D30.1 (K), D31.1 (K), D32.1 (K), U2.11 (D8/A8)
ROW3: D16.1 (K), D17.1 (K), U1.12 (~D9/A9)
ROW3_r: D33.1 (K), D34.1 (K), U2.12 (~D9/A9)
SCK: J4.4, J7.12, U1.6 (~D3)
SCK_r: J5.2, J8.12, U2.6 (~D3)
gnd: BatGND1.1, J1.1, J3.7, J4.2, J7.2, RSW1.1, U1.3 (GND), U1.4 (GND), U1.23 (GND)
gnd_r: BatGNDr1.1, J2.1, J5.4, J6.7, J8.2, RSW2.1, U2.3 (GND), U2.4 (GND), U2.23 (GND)
raw: SW_POWER1.3 (C), U1.24 (RAW)
raw_r: SW_POWERR1.3 (C), U2.24 (RAW)
reset: RSW1.2, U1.22 (RST)
reset_r: RSW2.2, U2.22 (RST)
vcc: J3.1, J4.3, J7.1, J7.6, U1.21 (VCC)
vcc_r: J5.3, J6.1, J8.1, J8.6, U2.21 (VCC)

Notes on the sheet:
Peripherals
Right Side (Peripheral)
Battery
Left Side (Main)
Reset
Nice!Nano
